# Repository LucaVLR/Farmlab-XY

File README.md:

# Farmlab-XY
Repository die alle code bevat voor de realisatie van het XY systeem

Docsify link:
https://lucavlr.github.io/Farmlab-XY/#/

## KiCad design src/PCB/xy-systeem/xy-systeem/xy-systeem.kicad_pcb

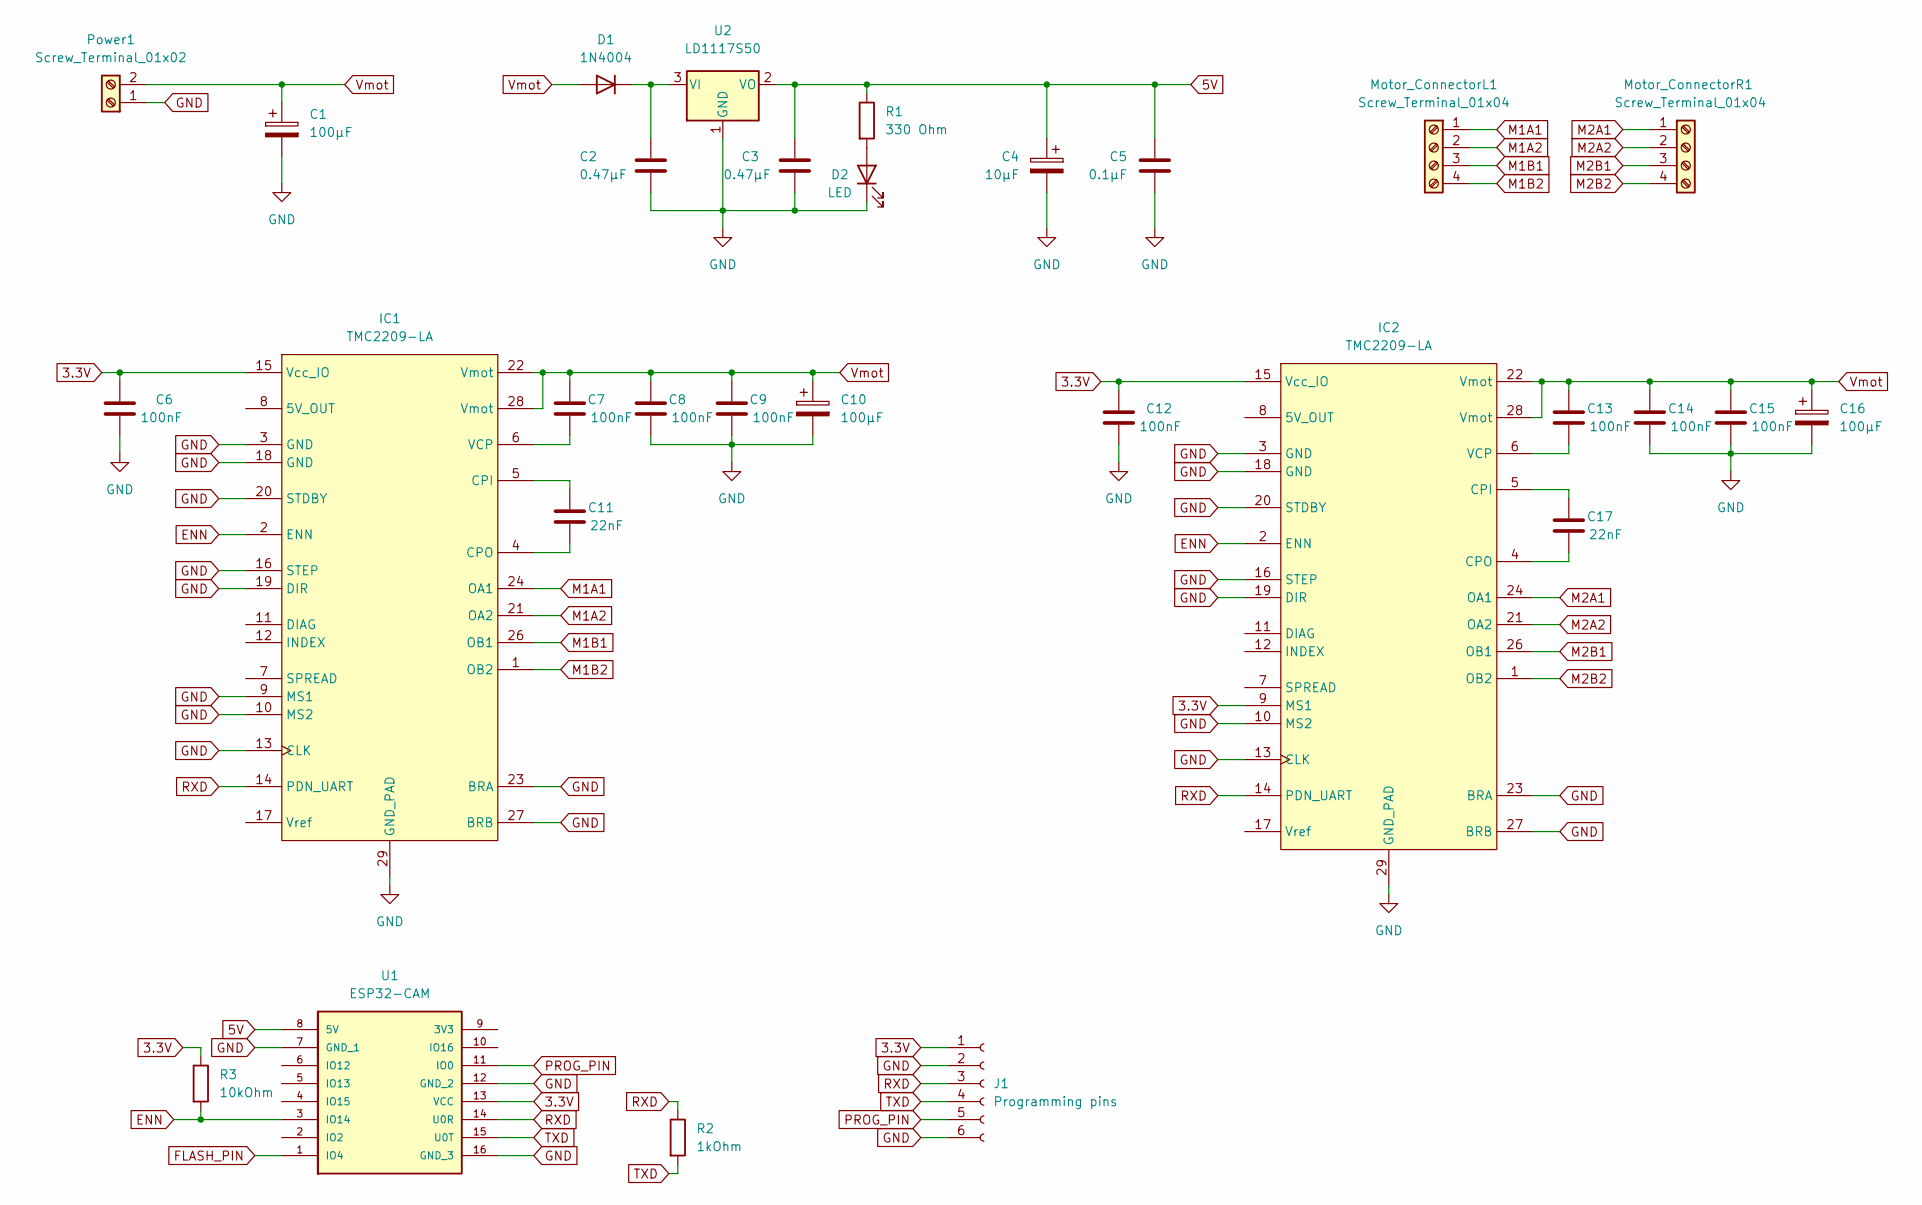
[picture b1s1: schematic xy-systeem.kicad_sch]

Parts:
C1, C10, C16: 100µF; CP_Radial_D8.0mm_P3.50mm
C2, C3: 0.47µF; C_0805_2012Metric_Pad1.18x1.45mm_HandSolder
C4: 10µF; CP_Radial_D6.3mm_P2.50mm
C5: 0.1µF; C_0805_2012Metric_Pad1.18x1.45mm_HandSolder
C6, C7, C8, C9, C12, C13, C14, C15: 100nF; C_0805_2012Metric_Pad1.18x1.45mm_HandSolder
C11, C17: 22nF; C_0805_2012Metric_Pad1.18x1.45mm_HandSolder
D1: 1N4004; D_DO-41_SOD81_P10.16mm_Horizontal
D2: LED; LED_0805_2012Metric_Pad1.15x1.40mm_HandSolder
IC1, IC2: TMC2209-LA
J1: Programming pins; PinHeader_1x06_P2.54mm_Horizontal
Motor_ConnectorL1: Screw_Terminal_01x04; TerminalBlock_bornier-4_P5.08mm
Motor_ConnectorR1: Screw_Terminal_01x04; TerminalBlock_bornier-4_P5.08mm
Power1: Screw_Terminal_01x02; TerminalBlock_bornier-2_P5.08mm
R1: 330 Ohm; R_0805_2012Metric_Pad1.20x1.40mm_HandSolder
R2: 1kOhm; R_0805_2012Metric_Pad1.20x1.40mm_HandSolder
R3: 10kOhm; R_0805_2012Metric_Pad1.20x1.40mm_HandSolder
U1: ESP32-CAM; MANUFACTURER_PART_NUMBER ESP32-CAM
U2: LD1117S50; SOT-223-3_TabPin2

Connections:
3.3V: C6.1, C12.1, IC1.15 (Vcc_IO), IC2.9 (MS1), IC2.15 (Vcc_IO), J1.1, R3.1, U1.13 (VCC)
5V: C3.1, C4.1, C5.1, R1.1, U1.8 (5V), U2.2 (VO)
ENN: IC1.2 (ENN), IC2.2 (ENN), R3.2, U1.3 (IO14)
FLASH_PIN: U1.1 (IO4)
GND: C1.2, C2.2, C3.2, C4.2, C5.2, C6.2, C8.2, C9.2, C10.2, C12.2, C14.2, C15.2, C16.2, D2.1 (K), IC1.3 (GND), IC1.9 (MS1), IC1.10 (MS2), IC1.13 (CLK), IC1.16 (STEP), IC1.18 (GND), IC1.19 (DIR), IC1.20 (STDBY), IC1.23 (BRA), IC1.27 (BRB), IC1.29 (GND_PAD), IC2.3 (GND), IC2.10 (MS2), IC2.13 (CLK), IC2.16 (STEP), IC2.18 (GND), IC2.19 (DIR), IC2.20 (STDBY), IC2.23 (BRA), IC2.27 (BRB), IC2.29 (GND_PAD), J1.2, J1.6, Power1.1, U1.7 (GND_1), U1.12 (GND_2), U1.16 (GND_3), U2.1 (GND)
M1A1: IC1.24 (OA1), Motor_ConnectorL1.1; also elsewhere on the board
M1A2: IC1.21 (OA2), Motor_ConnectorL1.2; also elsewhere on the board
M1B1: IC1.26 (OB1), Motor_ConnectorL1.3; also elsewhere on the board
M1B2: IC1.1 (OB2), Motor_ConnectorL1.4; also elsewhere on the board
M2A1: IC2.24 (OA1), Motor_ConnectorR1.1; also elsewhere on the board
M2A2: IC2.21 (OA2), Motor_ConnectorR1.2; also elsewhere on the board
M2B1: IC2.26 (OB1), Motor_ConnectorR1.3; also elsewhere on the board
M2B2: IC2.1 (OB2), Motor_ConnectorR1.4; also elsewhere on the board
unnamed: C2.1, D1.1 (K), U2.3 (VI)
unnamed: C7.2, IC1.6 (VCP)
unnamed: C11.1, IC1.5 (CPI)
unnamed: C11.2, IC1.4 (CPO)
unnamed: C13.2, IC2.6 (VCP)
unnamed: C17.1, IC2.5 (CPI)
unnamed: C17.2, IC2.4 (CPO)
unnamed: D2.2 (A), R1.2
PROG_PIN: J1.5, U1.11 (IO0)
RXD: IC1.14 (PDN_UART), IC2.14 (PDN_UART), J1.3, R2.1, U1.14 (U0R)
TXD: J1.4, R2.2, U1.15 (U0T)
Vmot: C1.1, C7.1, C8.1, C9.1, C10.1, C13.1, C14.1, C15.1, C16.1, D1.2 (A), IC1.22 (Vmot), IC1.28 (Vmot), IC2.22 (Vmot), IC2.28 (Vmot), Power1.2

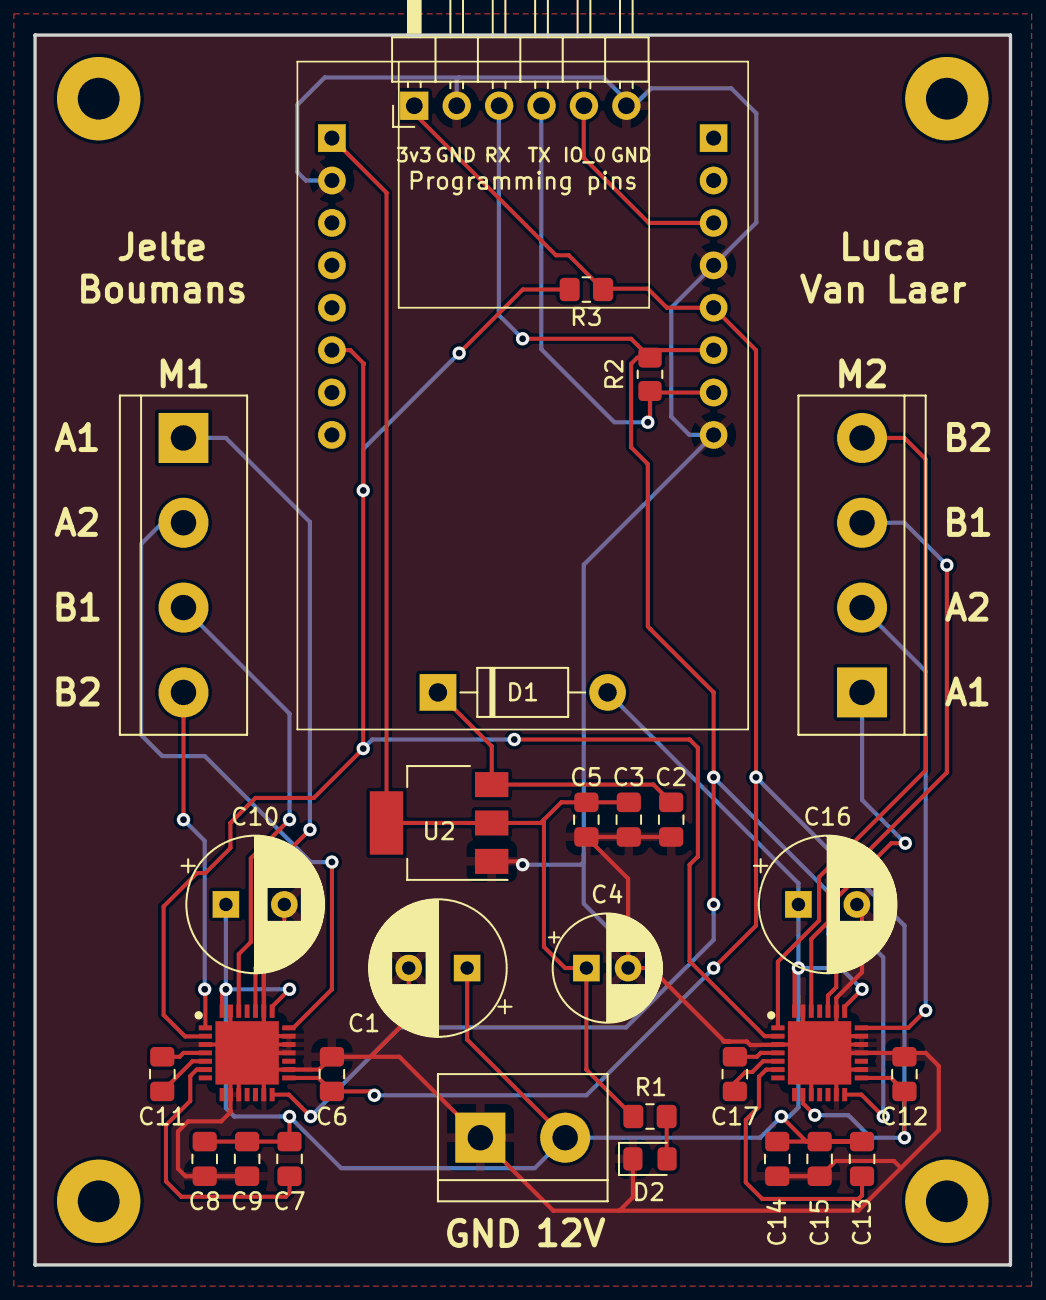
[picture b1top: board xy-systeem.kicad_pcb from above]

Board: 2 copper layers, 58.4 x 73.7 mm, 30 parts (0 on the bottom side), 24 nets.

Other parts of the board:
Motor_ConnectorL: Screw_Terminal_01x04; TerminalBlock_bornier-4_P5.08mm
Motor_ConnectorR: Screw_Terminal_01x04; TerminalBlock_bornier-4_P5.08mm

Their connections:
M1A1: Motor_ConnectorL.1; also elsewhere on the board
M1A2: Motor_ConnectorL.2; also elsewhere on the board
M1B1: Motor_ConnectorL.3; also elsewhere on the board
M1B2: Motor_ConnectorL.4; also elsewhere on the board
M2A1: Motor_ConnectorR.1; also elsewhere on the board
M2A2: Motor_ConnectorR.2; also elsewhere on the board
M2B1: Motor_ConnectorR.3; also elsewhere on the board
M2B2: Motor_ConnectorR.4; also elsewhere on the board

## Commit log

2022-06-13 Create Temp
2022-06-13 TMC bibliotheek toegevoegd
2022-06-13 Link naar nodered flow toegevoegd
2022-10-07 Fixed green tint issue
2022-10-07 Added function
    Moved picture taking and encoding to separate function 'takeEncodePicture' of type void
2022-10-07 removed redundant libraries
2022-10-07 fixed brown out issue
2022-10-07 Removed mqtt debugging
2022-10-07 Update calibratie_foto_demo.ino
    WiFi veranderd
    boot up camera calibratie toegevoegd
2022-10-14 Changed MQTT buffer size
2022-10-14 added new nodered flow
2022-10-23 add auto route
2022-10-27 Created docsify init
2022-10-27 Finished doc v1 main page
2022-10-27 fix(?) dashes
2022-10-28 File migration to src folder
2022-10-28 Added QFN soldering pictures
2022-12-02 PCB update - MAIN update
2022-12-02 Crashes + Diff steprate fixed
2022-12-16 removed velocity multiplier
2022-12-16 added autoroute V1
2022-12-23 Useless
2022-12-23 Added camera function
2023-01-11 node red final added
2023-01-18 Added documentation
2023-01-18 Grammar fix
